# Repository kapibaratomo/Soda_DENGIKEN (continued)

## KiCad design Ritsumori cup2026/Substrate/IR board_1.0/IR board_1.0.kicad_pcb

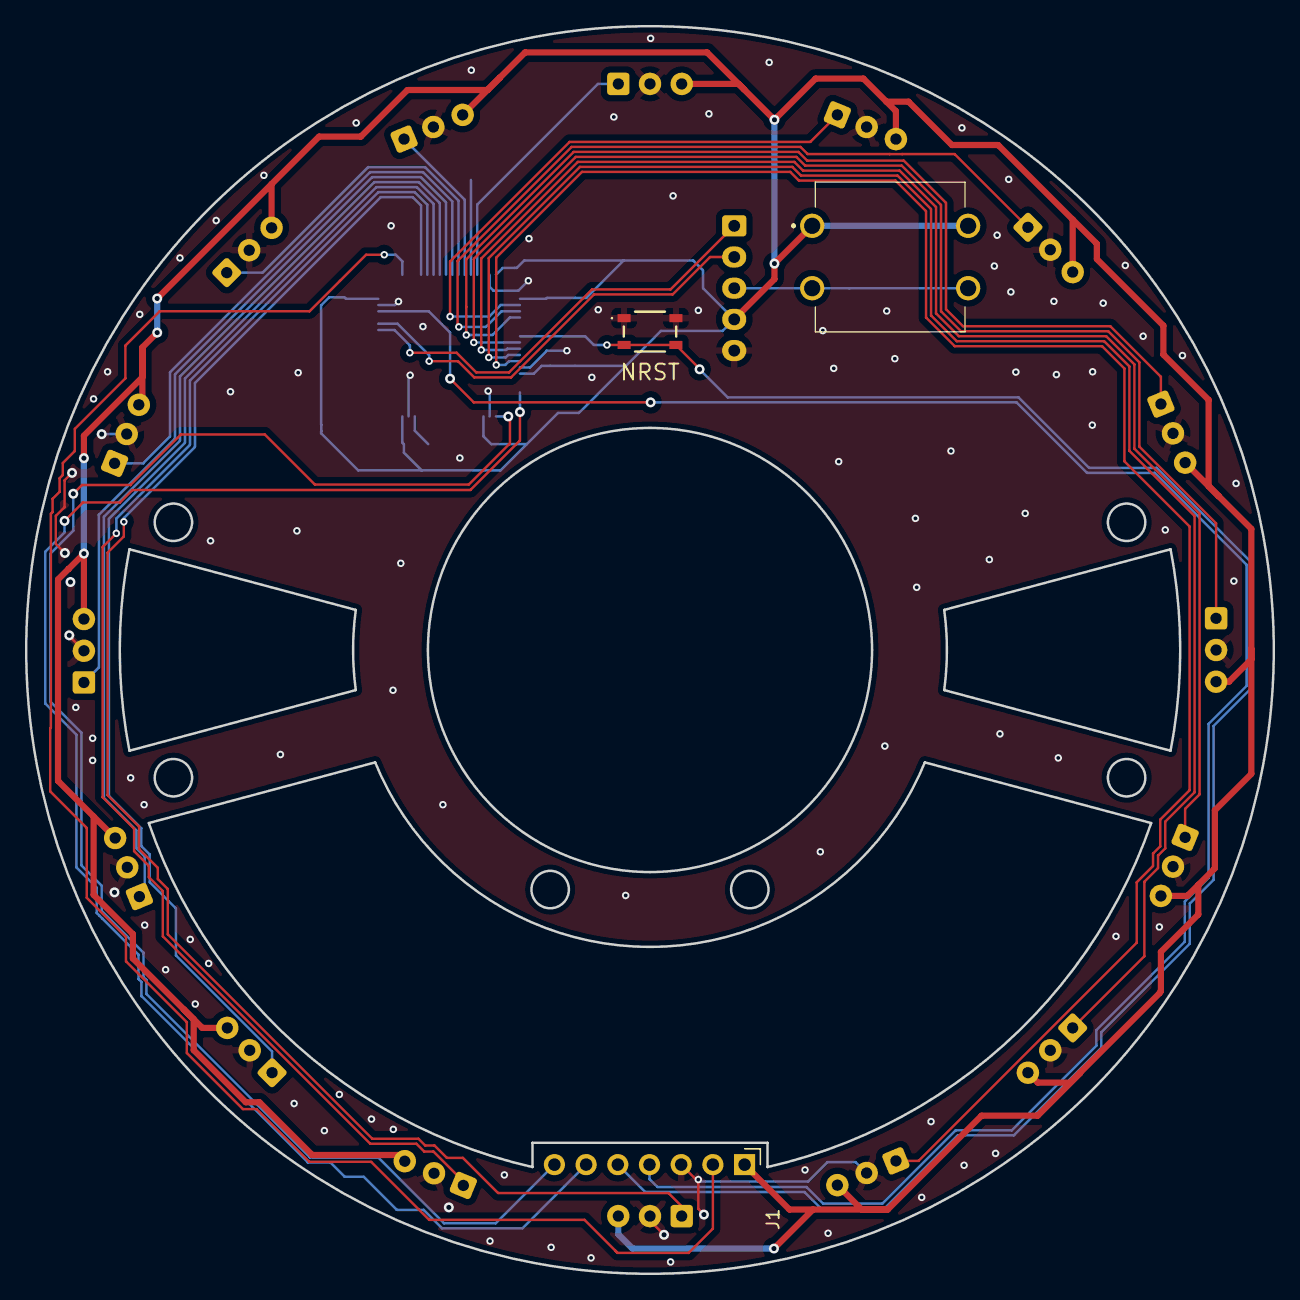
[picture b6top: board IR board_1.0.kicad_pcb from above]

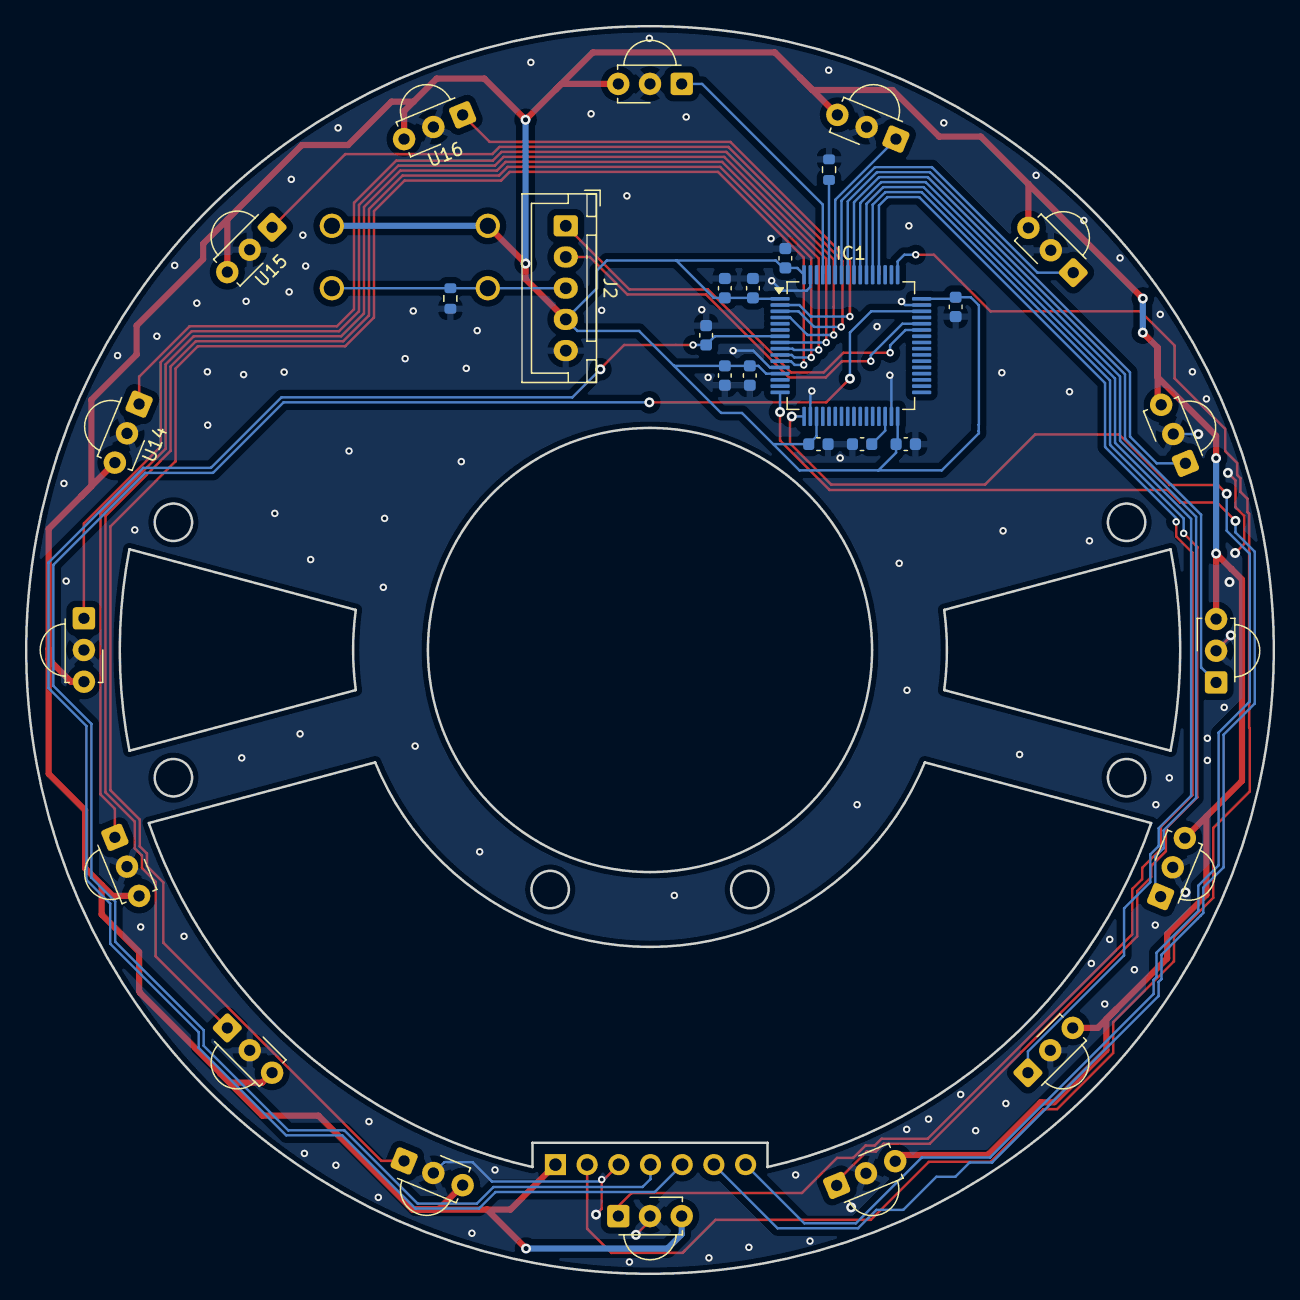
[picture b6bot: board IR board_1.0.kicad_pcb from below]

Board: 2 copper layers, 100.0 x 100.0 mm, 33 parts (30 on the bottom side), 28 nets.

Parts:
C1: 1; C_0603_1608Metric
C2, C4, C5, C6, C8#2, C9: 0.1; C_0603_1608Metric
C3: 4.7; C_0603_1608Metric
C7: 22u; C_0603_1608Metric
C8: 0.1u; C_0603_1608Metric
IC1: STM32F446RET6; LQFP-64_10x10mm_P0.5mm
J1: PC; PinHeader_1x07_P2.54mm_Horizontal
J2: main; JST_XH_B5B-XH-A_1x05_P2.50mm_Vertical
NRST: SW_Push; SKRPABE010
R1, R2: 10k; R_0603_1608Metric
SW2: SW_Push; TVGP01-G73BB
U1, U2, U3, U4, U5, U6, U7, U8, U9, U10, U11, U12, U13, U14, U15, U16: TSSP4038; Vishay_MINICAST-3Pin

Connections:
GND: C1.2, C2.2, C3.2, C4.2, C5.2, C6.1, C7.2, C8.2, C8#2.2, C9.2, IC1.12 (VSSA/VREF-), IC1.18 (VSS_1), IC1.31 (VSS_2), IC1.47 (VSS_3), IC1.63 (VSS_4), J1.3, J2.5, NRST.1, R1.1, R2.2, U1.2 (GND), U2.2 (GND), U3.2 (GND), U4.2 (GND), U5.2 (GND), U6.2 (GND), U7.2 (GND), U8.2 (GND), U9.2 (GND), U10.2 (GND), U11.2 (GND), U12.2 (GND), U13.2 (GND), U14.2 (GND), U15.2 (GND), U16.2 (GND)
IR_0: IC1.61 (PB8), U1.1 (OUT)
IR_1: IC1.59 (PB7), U2.1 (OUT)
IR_2: IC1.58 (PB6), U3.1 (OUT)
IR_3: IC1.57 (PB5), U4.1 (OUT)
IR_4: IC1.56 (PB4), U5.1 (OUT)
IR_5: IC1.55 (PB3), U6.1 (OUT)
IR_6: IC1.54 (PD2), U7.1 (OUT)
IR_7: IC1.53 (PC12), U8.1 (OUT)
IR_8: IC1.52 (PC11), U9.1 (OUT)
IR_9: IC1.11 (PC3), U10.1 (OUT)
IR_10: IC1.10 (PC2), U11.1 (OUT)
IR_11: IC1.9 (PC1), U12.1 (OUT)
IR_12: IC1.8 (PC0), U13.1 (OUT)
IR_13: IC1.4 (PC15-OSC32_OUT), U14.1 (OUT)
IR_14: IC1.3 (PC14-OSC32_IN), U15.1 (OUT)
IR_15: IC1.2 (PC13), U16.1 (OUT)
NRST: C6.2, IC1.7 (NRST), J1.5, NRST.2
unnamed: IC1.60 (BOOT0), R1.2
unnamed: C7.1, IC1.30 (VCAP_1)
SWCLK: IC1.49 (PA14), J1.2
SWDIO: IC1.46 (PA13), J1.4
UI_SW: J2.3, R2.1, SW2.2
USART1_RX_IR: IC1.44 (PA11), J2.2
USART1_TX_IR: IC1.43 (PA10), J2.1
USART2_RX_PC: IC1.17 (PA3), J1.7
USART2_TX_PC: IC1.16 (PA2), J1.6
VCC: C1.1, C2.1, C3.1, C4.1, C5.1, C8.1, C8#2.1, C9.1, IC1.1 (VBAT), IC1.13 (VDDA/VREF+), IC1.19 (VDD_1), IC1.32 (VDD_2), IC1.48 (VDD_3), IC1.64 (VDD_4), J1.1, J2.4, SW2.1, U1.3 (Vs), U2.3 (Vs), U3.3 (Vs), U4.3 (Vs), U5.3 (Vs), U6.3 (Vs), U7.3 (Vs), U8.3 (Vs), U9.3 (Vs), U10.3 (Vs), U11.3 (Vs), U12.3 (Vs), U13.3 (Vs), U14.3 (Vs), U15.3 (Vs), U16.3 (Vs)

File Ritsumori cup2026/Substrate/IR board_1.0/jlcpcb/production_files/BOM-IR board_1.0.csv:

Comment,Designator,Footprint,LCSC,Quantity
0.1,"C2,C4,C5,C6,C9",C_0603_1608Metric,C14663,5
1,C1,C_0603_1608Metric,C15849,1
10k,"R1,R2",R_0603_1608Metric,C25804,2
22u,C7,C_0603_1608Metric,C59461,1
4.7,C3,C_0603_1608Metric,C19666,1
STM32F446RET6,IC1,LQFP-64_10x10mm_P0.5mm,C69336,1
TSSP4038,U2,Vishay_MINICAST-3Pin,,1
TSSP4038,U3,Vishay_MINICAST-3Pin,,1
TSSP4038,U8,Vishay_MINICAST-3Pin,,1
0.1,C8,C_0603_1608Metric,,1
SW_Push,SW2,TVGP01-G73BB,,1
TSSP4038,U12,Vishay_MINICAST-3Pin,,1
TSSP4038,U10,Vishay_MINICAST-3Pin,,1
TSSP4038,U9,Vishay_MINICAST-3Pin,,1
TSSP4038,U5,Vishay_MINICAST-3Pin,,1
TSSP4038,U14,Vishay_MINICAST-3Pin,,1
TSSP4038,U6,Vishay_MINICAST-3Pin,,1
TSSP4038,U4,Vishay_MINICAST-3Pin,,1
TSSP4038,U11,Vishay_MINICAST-3Pin,,1
TSSP4038,U7,Vishay_MINICAST-3Pin,,1
TSSP4038,U16,Vishay_MINICAST-3Pin,,1
TSSP4038,U15,Vishay_MINICAST-3Pin,,1
TSSP4038,U13,Vishay_MINICAST-3Pin,,1
TSSP4038,U1,Vishay_MINICAST-3Pin,,1
PC,J1,PinHeader_1x07_P2.54mm_Horizontal,,1
main,J2,JST_XH_B5B-XH-A_1x05_P2.50mm_Vertical,,1
SW_Push,NRST,SKRPABE010,,1

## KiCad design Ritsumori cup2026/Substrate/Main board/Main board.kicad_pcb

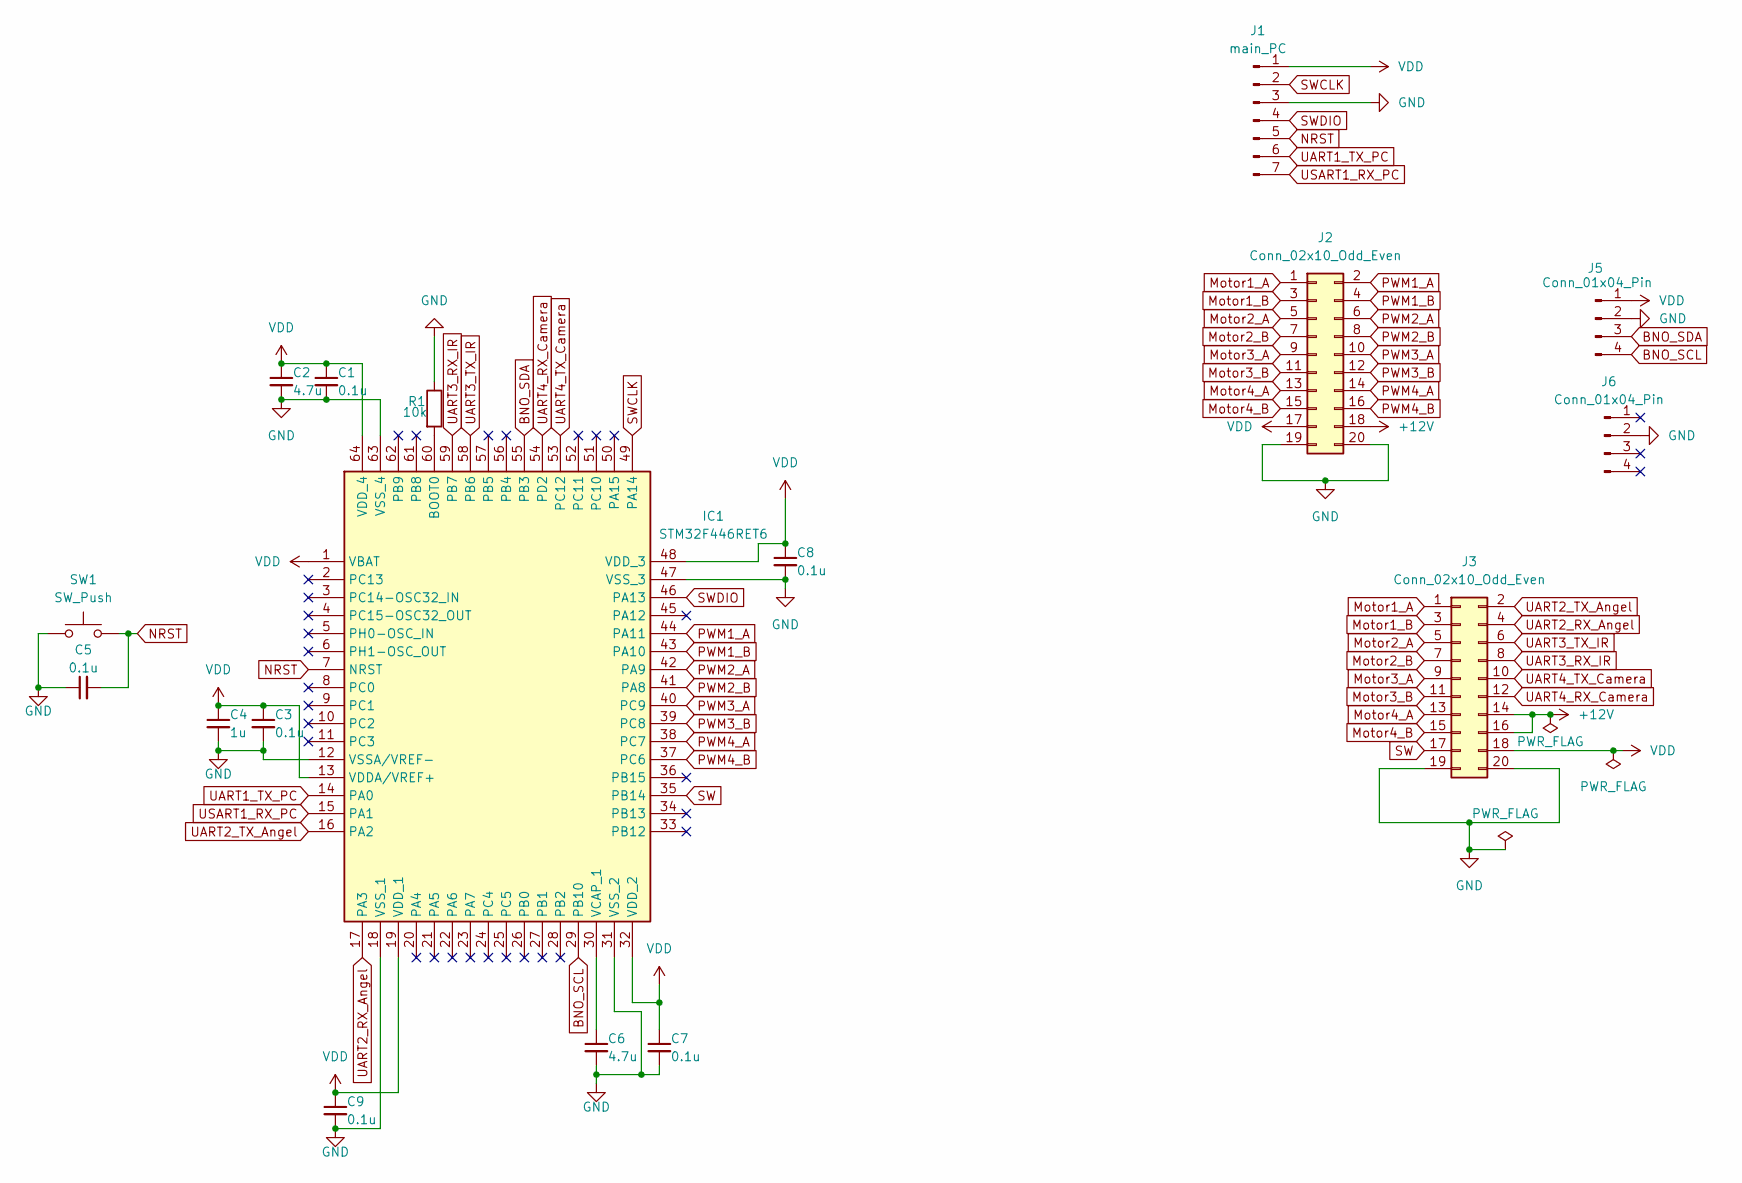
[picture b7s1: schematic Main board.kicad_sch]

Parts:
C1, C3, C5, C7, C8, C9: 0.1u; C_0603_1608Metric
C2, C6: 4.7u; C_0603_1608Metric
C4: 1u; C_0603_1608Metric
IC1: STM32F446RET6; LQFP-64_10x10mm_P0.5mm; Manufacturer_Part_Number STM32F446RET6; Mouser Part Number 511-STM32F446RET6
J1: main_PC; PinHeader_1x07_P2.54mm_Vertical
J2: Conn_02x10_Odd_Even; PinHeader_2x10_P2.54mm_Vertical
J3: Conn_02x10_Odd_Even; IDC-Header_2x10_P2.54mm_Vertical
J5, J6: Conn_01x04_Pin; PinSocket_1x04_P2.54mm_Vertical
R1: 10k; R_0603_1608Metric
SW1: SW_Push; SKRPABE010

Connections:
+12V: J2.18, J3.14, J3.16
BNO_SCL: IC1.29 (PB10), J5.4
BNO_SDA: IC1.55 (PB3), J5.3
GND: C1.2, C2.2, C3.2, C4.2, C5.1, C6.2, C7.2, C8.2, C9.2, IC1.12 (VSSA/VREF-), IC1.18 (VSS_1), IC1.31 (VSS_2), IC1.47 (VSS_3), IC1.63 (VSS_4), J1.3, J2.19, J2.20, J3.19, J3.20, J5.2, J6.2, R1.1, SW1.1
Motor1_A: J2.1, J3.1
Motor1_B: J2.3, J3.3
Motor2_A: J2.5, J3.5
Motor2_B: J2.7, J3.7
Motor3_A: J2.9, J3.9
Motor3_B: J2.11, J3.11
Motor4_A: J2.13, J3.13
Motor4_B: J2.15, J3.15
NRST: C5.2, IC1.7 (NRST), J1.5, SW1.2
unnamed: IC1.60 (BOOT0), R1.2
unnamed: C6.1, IC1.30 (VCAP_1)
PWM1_A: IC1.44 (PA11), J2.2
PWM1_B: IC1.43 (PA10), J2.4
PWM2_A: IC1.42 (PA9), J2.6
PWM2_B: IC1.41 (PA8), J2.8
PWM3_A: IC1.40 (PC9), J2.10
PWM3_B: IC1.39 (PC8), J2.12
PWM4_A: IC1.38 (PC7), J2.14
PWM4_B: IC1.37 (PC6), J2.16
SW: IC1.35 (PB14), J3.17
SWCLK: IC1.49 (PA14), J1.2
SWDIO: IC1.46 (PA13), J1.4
UART1_TX_PC: IC1.14 (PA0), J1.6
UART2_RX_Angel: IC1.17 (PA3), J3.4
UART2_TX_Angel: IC1.16 (PA2), J3.2
UART3_RX_IR: IC1.59 (PB7), J3.8
UART3_TX_IR: IC1.58 (PB6), J3.6
UART4_RX_Camera: IC1.54 (PD2), J3.12
UART4_TX_Camera: IC1.53 (PC12), J3.10
USART1_RX_PC: IC1.15 (PA1), J1.7
VDD: C1.1, C2.1, C3.1, C4.1, C7.1, C8.1, C9.1, IC1.1 (VBAT), IC1.13 (VDDA/VREF+), IC1.19 (VDD_1), IC1.32 (VDD_2), IC1.48 (VDD_3), IC1.64 (VDD_4), J1.1, J2.17, J3.18, J5.1

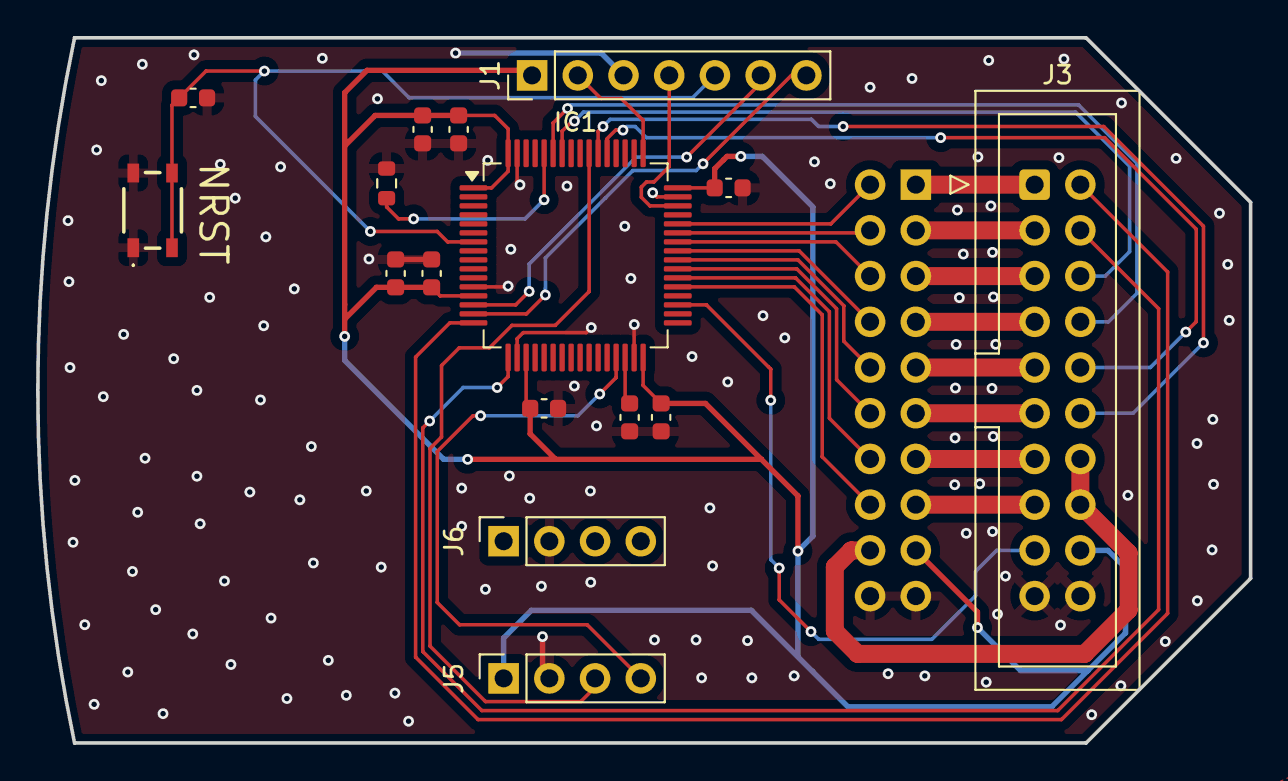
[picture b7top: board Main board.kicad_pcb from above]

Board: 2 copper layers, 67.4 x 39.2 mm, 17 parts (1 on the bottom side), 35 nets.

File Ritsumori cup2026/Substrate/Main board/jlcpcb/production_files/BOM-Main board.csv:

Comment,Designator,Footprint,LCSC,Quantity
0.1u,"C1,C3,C5,C7,C8,C9",C_0603_1608Metric,C14663,6
10k,R1,R_0603_1608Metric,C25804,1
1u,C4,C_0603_1608Metric,C15849,1
22u,C6,C_0603_1608Metric,C59461,1
4.7u,C2,C_0603_1608Metric,C19666,1
STM32F446RET6,IC1,LQFP-64_10x10mm_P0.5mm,C69336,1
Conn_02x10_Odd_Even,J3,IDC-Header_2x10_P2.54mm_Vertical,,1
main_PC,J1,PinHeader_1x07_P2.54mm_Vertical,,1
SW_Push,SW1,SKRPABE010,,1
Conn_01x04_Pin,J6,PinSocket_1x04_P2.54mm_Vertical,,1
Conn_01x04_Pin,J5,PinSocket_1x04_P2.54mm_Vertical,,1
Conn_02x10_Odd_Even,J2,PinHeader_2x10_P2.54mm_Vertical,,1
